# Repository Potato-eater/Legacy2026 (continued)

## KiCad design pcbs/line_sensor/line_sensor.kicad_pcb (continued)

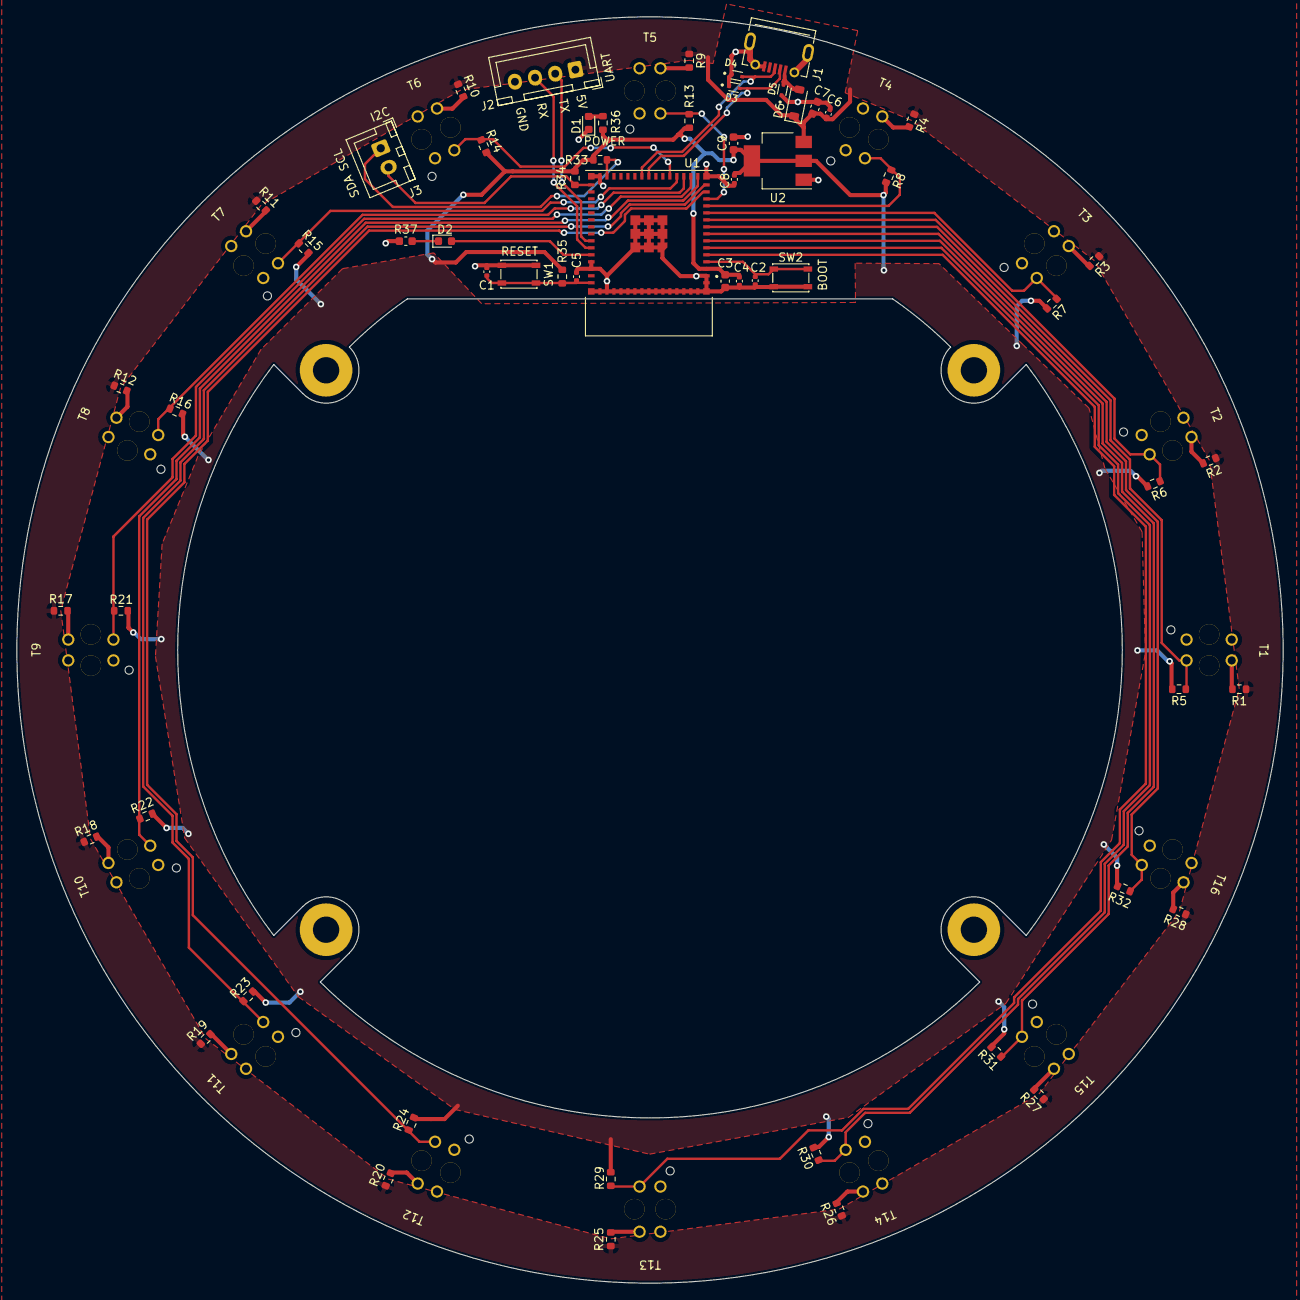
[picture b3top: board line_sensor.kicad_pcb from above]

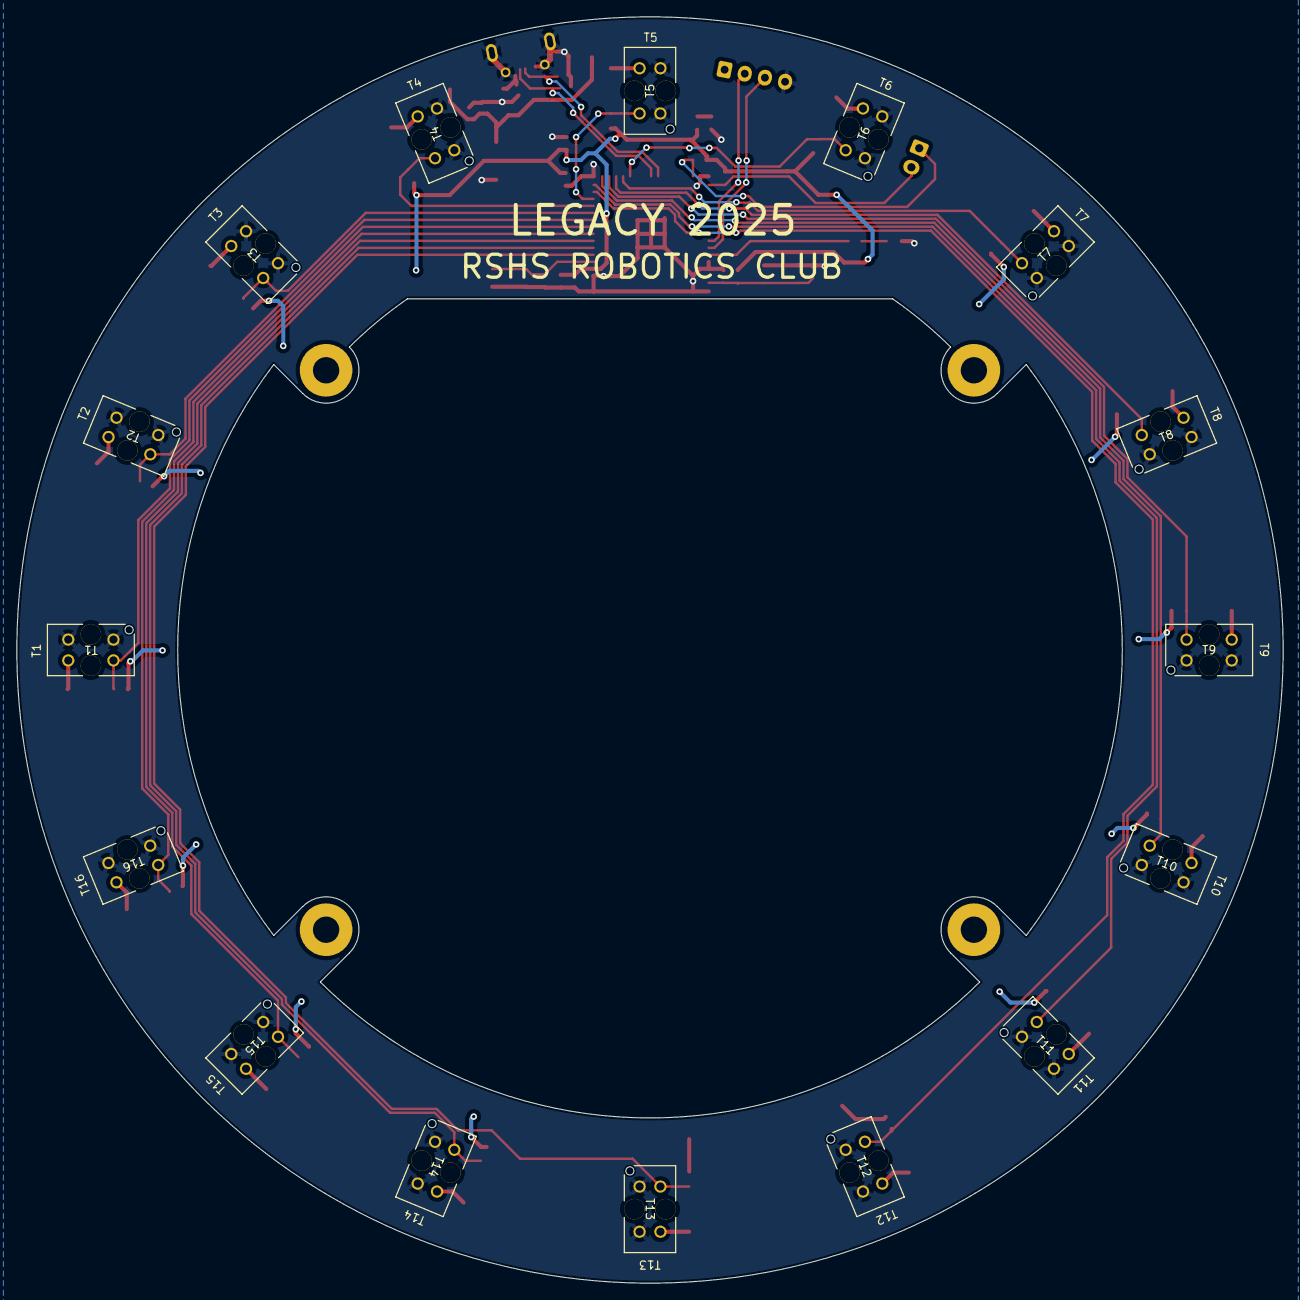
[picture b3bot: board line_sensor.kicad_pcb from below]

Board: 2 copper layers, 154.0 x 154.0 mm, 79 parts (16 on the bottom side), 47 nets.

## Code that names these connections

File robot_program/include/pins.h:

// this file defines all the digital pins.

// drive motors
#define TL_PWM 33
#define TL_DIR 34
#define TR_PWM 29
#define TR_DIR 31
#define BL_PWM 22
#define BL_DIR 23
#define BR_PWM 2
#define BR_DIR 3

// run button
#define BTN_RUN 5

// debugging led
#define DEBUG_LED 17
#define TEENSY_LED 13

#define BTN_1 6 // front button
#define BTN_2 12 // left button
#define BTN_3 10 // center button
#define BTN_4 9 // right button
#define BTN_5 11 // back button

#define DR_PWM 7
#define DR_DIR 8

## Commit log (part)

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2026-04-11 added ir sensor and ir visualiser
2026-06-10 updated some code
2026-06-10 adding robot_program
